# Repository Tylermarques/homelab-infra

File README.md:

# Tyler's Homelab

## DNS for local services (`*.local.tylermarques.com`)

Local services resolve for both home-LAN and tailnet clients via public DNS:

- A wildcard A record `*.local.tylermarques.com` (in `rackspace/apps/dns.py`,
  controlled by `HOME_LAN_INGRESS_IP` in `rackspace/.env`) points at the home
  cluster's Traefik LAN IP. It is unproxied — anyone can resolve it, but only
  clients on the LAN or tailnet can route to it.
- A Tailscale `Connector` (subnet router, `homecluster/tailscale/`, synced by
  the `tailscale` Argo CD Application) advertises the LAN subnet
  (`HOME_LAN_SUBNET`) to the tailnet, so tailnet clients can reach that LAN IP.
  The route must be approved once in the Tailscale admin console (or
  auto-approved via ACL `autoApprovers`).
- TLS comes from the existing `*.local.tylermarques.com` wildcard cert
  (cert-manager DNS-01, `rackspace/apps/cert_manager/`).

Gotcha: some routers/resolvers drop public DNS answers containing private IPs
(rebind protection). If LAN clients can't resolve `*.local.tylermarques.com`,
whitelist the domain in the router's rebind-protection settings.

## TODOs

- [x] Move most of services to RackspaceSpot
- Implement secret manager
- Speed tests for the NFS - is it feasible to have the nfs at home?
- Dashboard with appropriate auto discovery
- Move the existing services over to pulumi

### Service migration List

- [] dashy
- [] freshrss
- [x] prometheus
- [x] grafana
- [] immich
- [] loki
- [] paperless-ngx
- [x] overseerr — replaced by Seerr (homecluster/seerr/), deployed via the
      official OCI Helm chart driven by ArgoCD. Reachable only internally at
      seerr.local.tylermarques.com; the public overseerr record was dropped.
- [] immich
- [] mealie
- [] ntfy

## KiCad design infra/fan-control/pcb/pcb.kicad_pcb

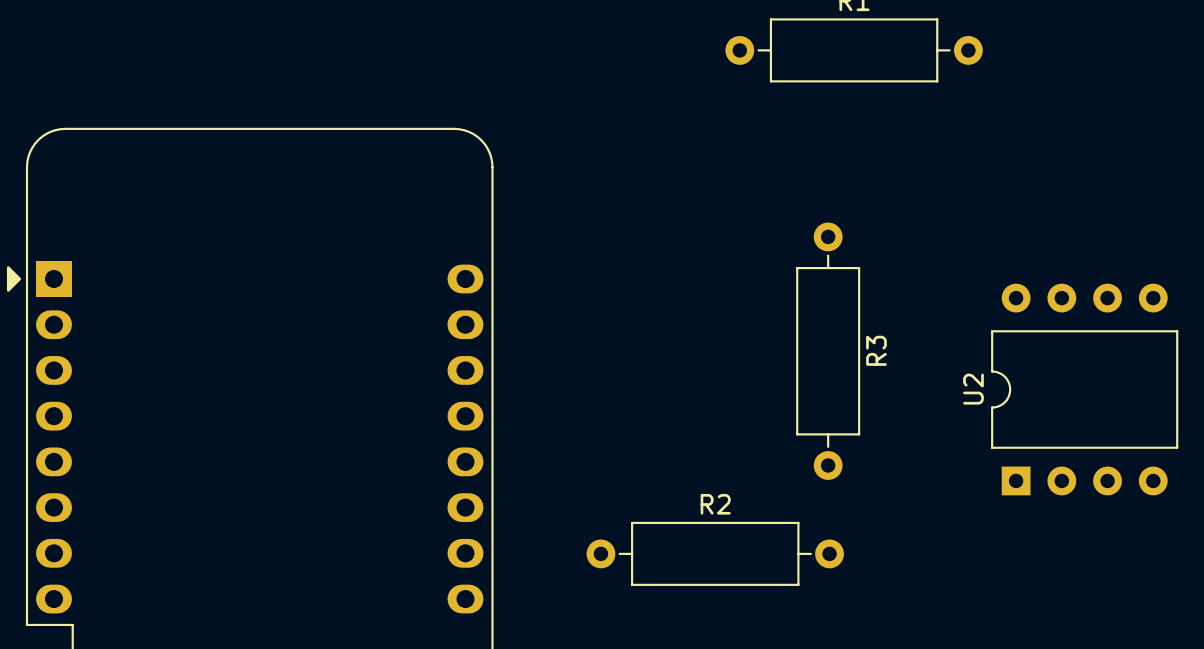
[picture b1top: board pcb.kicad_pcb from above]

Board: 2 copper layers, 5 parts (0 on the bottom side), 5 nets, no tracks yet.

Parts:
R1: 300; R_Axial_DIN0309_L9.0mm_D3.2mm_P12.70mm_Horizontal
R2: 110; R_Axial_DIN0309_L9.0mm_D3.2mm_P12.70mm_Horizontal
R3: 2.1k; R_Axial_DIN0309_L9.0mm_D3.2mm_P12.70mm_Horizontal
U1: WeMos_D1_mini; WEMOS_D1_mini_light
U2: LM358; DIP-8_W10.16mm

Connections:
GND: R2.1, U1.10 (GND)
unnamed: R1.1, U1.3 (D0)
unnamed: R1.2, U2.5 (+)
unnamed: R2.2, R3.2, U2.6 (-)
unnamed: R3.1, U2.7

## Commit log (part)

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2023-03-11 Added mealie, infra, and restructed
2023-08-25 Adding a bunch of services
2023-10-16 Added pod to monitor and update the speeds of the fans in the server rack, keep them quiet most of the time
2023-12-04 Updating to the main k8s-mediaserver-operator repo
2024-06-11 Adding u-the-bomb-com manifests
2024-06-11 Cleaning up tokens I committed like an idiot
2024-06-11 Removing some dirs and files from git
2024-06-11 Updating the operator, seeing if that helps argo clone the submodule
2024-06-11 Trying https instead
2024-06-12 Increment image tag
2024-06-12 Push from Tylermarques to Tylermarques/u-the-bomb-com
2024-06-21 Adding tylermarques.com manifests
2024-06-21 Push from Tylermarques to Tylermarques/tylermarques.com
2024-06-21 Fixing namespace
2024-06-21 Fixing route
2024-06-22 Adding websecure redirect
2024-06-24 Updating the host for tylermarques.com
2024-06-24 Copying redirect scheme from other working service
2024-09-06 file architecture for meeting-tools
2024-09-09 added secrets to meeting tools
2024-09-09 renamed meeting tools deployments and changed pvc to nfs for data
2024-09-09 Moved some meeting-notes "secrets" to configMap
2024-09-09 added todos and small fixes to meeting notes
2024-09-13 Added meeting-tools changes made from adding auth
2024-09-14 Updating so base is valid even if secrets don't exist
2024-09-14 Fixing secrets so it builds even with bad data
2024-09-14 Changing repo location
2024-09-14 Changing namespace
2024-09-14 Changing nfs mount to be outside library dir
2024-09-14 Push from Tylermarques to MarquesCG/meeting-tools
2024-09-14 Adding the image pull secret
2024-09-16 Fixing mongo key in CM
2024-09-16 Fixing prod meeting tools image names
2024-09-16 Updating configmaps to have correct varaibles
2024-09-16 Fixing missing configmap names
2024-09-26 Fixing model file key misname
2024-09-26 fixing model key
2024-09-26 Commenting out secrets because I can't be bothered. Making them manually
2024-09-26 Adding secret that was missing from dir watcher
2024-09-26 Updating urls for dev and prod
2024-09-26 Correcting the ingress
2024-09-27 Push from OwenWaldron to MarquesCG/meeting-tools
2024-10-02 Added mongodb manifests
2024-10-02 Added rabbitmq manifests
2024-10-02 Changed mongodb to use nfs over persistent volume
2024-11-18 Removed mongodb & rabbitmq. Each service should host its own
2024-11-20 Added cert managers for marquescg
2024-11-20 Removed staging and added meeting-tools
2024-12-04 Added MarquesCG to certmanager dns zones
2024-12-04 Deleted unused mongodb and rabbitmq
2024-12-04 Updated meeting-tools manifests
2024-12-04 Added marquescg manifests
2024-12-05 Adding TwentyCRM
2024-12-05 Updating to include all the google auth details
2024-12-06 Push from OwenWaldron to MarquesCG/Marquescg.com
2024-12-06 Updated certificate to right namespace
2024-12-12 Push from Tylermarques to MarquesCG/Marquescg.com
2024-12-16 Initializing service meeting-tools from OwenWaldron
2024-12-20 Updating freshrss ingress
2024-12-20 Adding tls-cert for argocd
2025-02-25 Adding IaC for cloudflare DNS
2025-02-25 Rearranging to better represent IaC
2025-04-03 Replacing containio traefik with regular version ingressroutes
2025-04-03 Adding the argo apps declaratively
2025-04-03 Removing containo from ingress routes
2025-04-03 Altering location of a bunch of the files. Getting ready for Pulumi
2025-04-03 Fixing us to io TLD
2025-04-03 Fixing tylermarques-com deployment
2025-04-03 Adding namespace to marquescg
2025-04-03 Fixing a missing namespace
2025-04-04 WIP: cert-manager refuses to come up, citing a badly named SVC
2025-04-15 Working setup of local NFS accessible to remote cloud as NFS PVs
    Goal being that I can continue to use the hardware I have at home,
    without needing to have remote traffic directed to my IP.
2025-04-17 Adding the working config for home NFS, remote Jellyfin.
    Still to go:
    - Speed tests, Jellyfin feels painfully slow right now, but it does
    work. I need to add something that will test the speed to the nfs
    regularly.
    - Adding the rest of the stack (lidarr, radarr, sonarr, etc.)
2025-04-17 Fixing bad manifest
2025-04-17 Added create_root to ingressRoute
    Now you can use the ingressRoute creator to create the root ingress
    route and it's matching certificate.
2025-04-21 Moving blogsite to cloud cluster.
2025-04-22 Adding basic monitoring to the cluster. Adjusting PV creation.
    I'd like to add better monitoring to the cluster space. Good place to
    start is prometheus and grafana. I've also added the beginnings of
    getting loki running.
2025-04-22 Test
2025-04-22 Updating README and removing old unused apps
2025-04-24 Fixes and ruff format
2025-04-29 Shuffling some directories to make obvious what lives where.
2025-05-02 Fixing mcg.com
2025-05-02 Fixes for mcg again
2025-05-02 Fixing rackspace deploy, and marquescg.com
2025-07-16 Fixing issues with www. not routing to host.tld
2025-07-23 Some of the deployments work, but still having issues mounting the nfs
2026-01-02 WIP: This got finished elsewhere, as of commit, running as docker services on Martha
2026-01-02 WIP: Moved to UV, adding cloudnative and auttheliea, and Mealie again
2026-01-13 Add Syncthing to the local cluster, with a mount to the NFS (vibe-kanban 3cba5a7b)
    We want to be able to sync specific directories across many machines, using syncthing should ensure that. It's storage should be a mount on the local drive, and it's data access should be as local as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
2026-01-13 Lets add a block storage option to the home cluster. (vibe-kanban d522d845)
    We want to be able to have a storage option on the home cluster that can operate with an S3 like API, as well as be regularly backed up. Please research appropriate options, then present them.
2026-01-18 It seems Pulumi up doesn't work in the homelab/ directory (vibe-kanban 771b44e5)
    try running uv run pulumi up in the homelab/ directory and diagnose then fix the issues
2026-01-18 Please add the Jellyseer stack to the homelab/ (vibe-kanban 50a468bf)
    https://docs.seerr.dev/
    Please go looking for the branch that include lidarr support, and implement that in homelab/apps/media/ .
2026-01-18 Exception: invoke of talos:machine/getConfiguration:getConfiguration failed: invocation of talos:machine/getConfiguration:getConfiguration returned an error: [AttributeName("machine_secrets").Attribu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
2026-01-26 Adding lidarr
2026-01-30 Updating docker compose to include jellyfin
2026-01-30 Remove need to specify schematic ID, update node ids and names
2026-01-30 Fix loopback address mixup, remove outstanding schematic id refs
2026-01-30 WIP: Checkpoint
